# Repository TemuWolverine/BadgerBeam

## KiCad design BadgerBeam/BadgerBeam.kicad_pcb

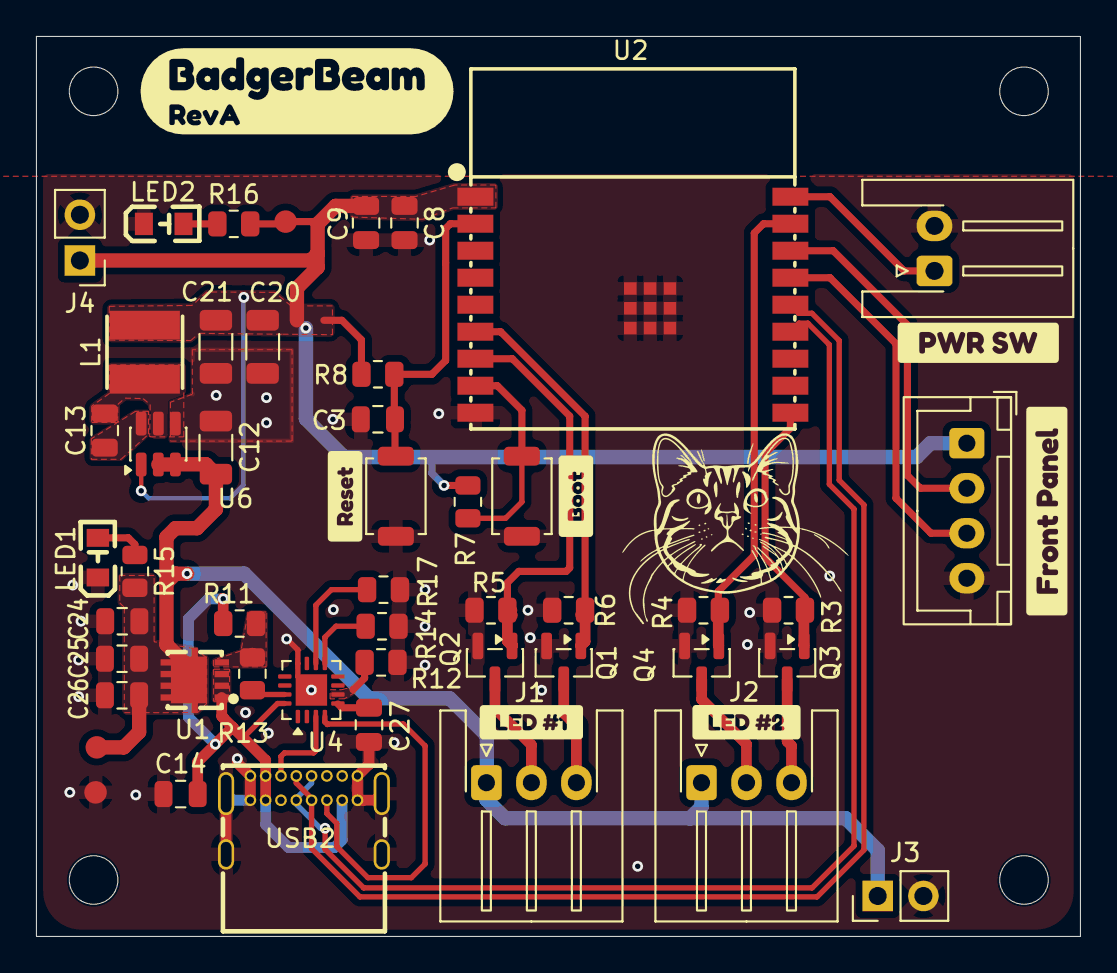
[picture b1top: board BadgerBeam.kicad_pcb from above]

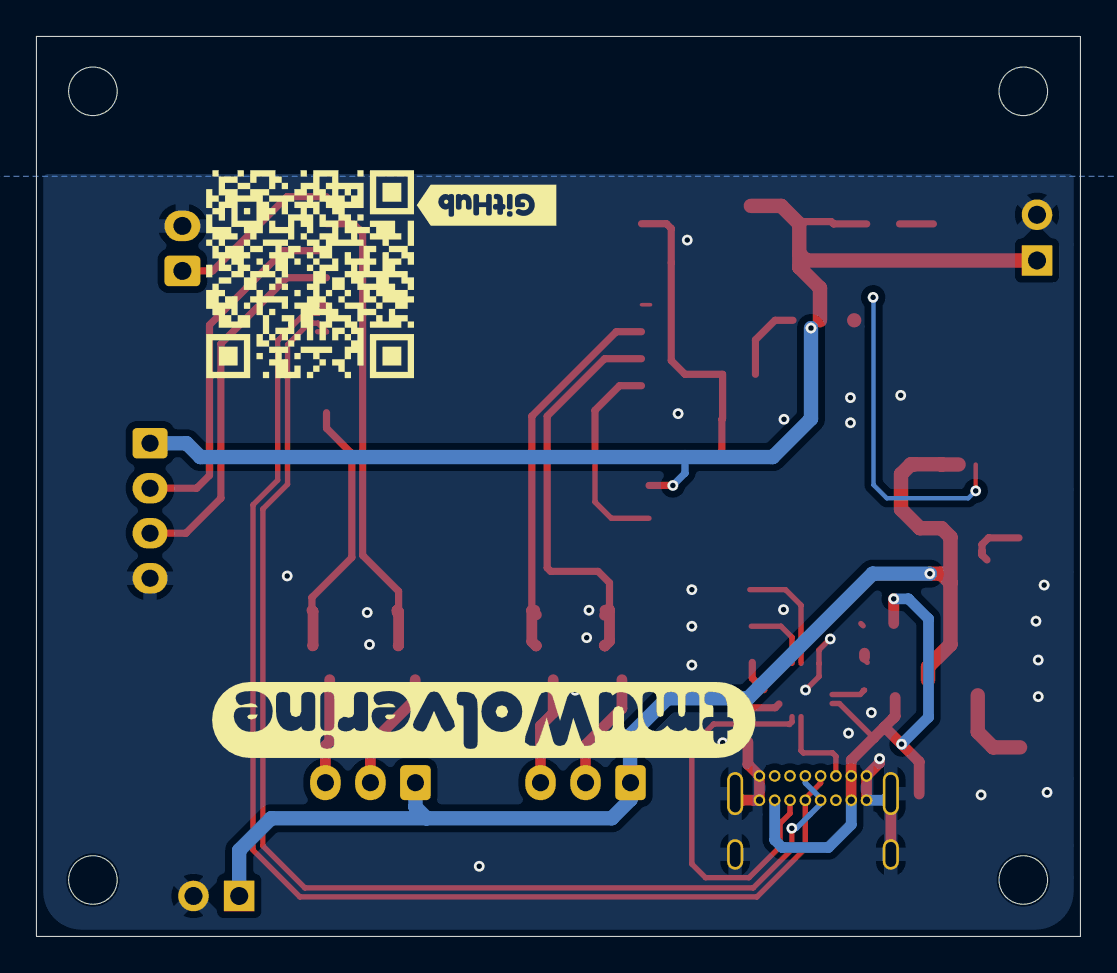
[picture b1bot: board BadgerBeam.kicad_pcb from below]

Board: 2 copper layers, 58.0 x 50.0 mm, 58 parts (3 on the bottom side), 31 nets.

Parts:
C3, C14, C27: 1uF; C_0805_2012Metric
C8: 10uF; C_0805_2012Metric
C9, C13: 100nF; C_0805_2012Metric
C12: 10uF; C_1206_3216Metric
C20, C21: 22uF; C_1206_3216Metric
C24, C25, C26: 4.7uF; C_0805_2012Metric
J1, J2: Conn_01x03_Pin; JST_XH_S3B-XH-A-1_1x03_P2.50mm_Horizontal
J3, J4: Conn_01x02_Pin; PinHeader_1x02_P2.54mm_Vertical
J5: Conn_01x04_Pin; JST_XH_B4B-XH-A_1x04_P2.50mm_Vertical
L1: 3.9μH; IND-SMD_L4.0-W4.0_FNR40XXS
LED1, LED2: LED0805-RD
Q1, Q2, Q3, Q4: AO3400A; SOT-23
R3, R4, R5, R6, R7, R8: 10k; R_0805_2012Metric
R11: 49.9k; R_0805_2012Metric
R12: 900k; R_0805_2012Metric
R13: 5.1k; R_0805_2012Metric
R14, R17: 6.04k; R_0805_2012Metric
R15: 20k; R_0805_2012Metric
R16: 2.4k; R_0805_2012Metric
SW1: SW_Push; JST_XH_S2B-XH-A-1_1x02_P2.50mm_Horizontal
SW3: Reset; SW_SPST_TS-1088-xR020
SW4: Boot; SW_SPST_TS-1088-xR020
TP1, TP2, TP3: TestPoint; TestPoint-1.25mm
U1: PRPAK-8_L3.0-W3.0-P0.65-BL-EP
U2: 2.4GHz; BULETM-SMD_ESPRESSIF_ESP32-C3-WROOM-02-N4-4MB
U4: HUSB238A-xxxxx-QN16R; WQFN-16-1EP_3x3mm_P0.5mm_EP1.75x1.75mm
U6: AP63203WU; TSOT-23-6
USB2: USB-C-TH_UC23-0B16F00P11
kobee-studio-6A97AC47: Kobee Studio; kobee-studio-6A97AC2D
kobee-studio-6A97AC75: Kobee Studio; kobee-studio-6A97AC75
kobee-studio-6AED3B48: Kobee Studio; kobee-studio-6A96C1A4
kobee-studio-6AED3B77: Kobee Studio; kobee-studio-6A97ABF4
kobee-studio-6AF1A8A9, kobee-studio-6AF1A89F, kobee-studio-6AF1A91A, kobee-studio-6AF1A872, kobee-studio-6AF1A910, kobee-studio-6AF03576: Kobee Studio; kobee-studio-6AEAEE22

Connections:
+3V3: C8.1, C9.1, C20.1, C21.1, J4.1, J5.1, L1.2, R7.1, R8.1, R16.2, TP3.1 (1_1), U2.1 (3V3), U6.1 (FB)
/Power/VBUS: C14.2, R11.2, U1.1 (S), U1.2 (S), U1.3 (S), U4.16 (VBUS), USB2.A4 (VBUS), USB2.B4 (VBUS), USB2.B9 (VBUS)
CC1: U4.3 (CC1), USB2.A5 (CC1)
CC2: U4.4 (CC2), USB2.B5 (CC2)
CW_1: Q1.1 (G), R6.2, U2.6 (IO7)
CW_2: Q3.1 (G), R3.1, U2.10 (IO10)
GND: C3.2, C8.2, C9.2, C12.2, C14.1, C20.2, C21.2, C24.2, C25.2, C26.2, C27.1, J3.2, J4.2, J5.4, LED1.1 (K), LED2.1 (K), Q1.2 (S), Q2.2 (S), Q3.2 (S), Q4.2 (S), R3.2, R4.2, R5.2, R6.1, R12.1, R14.2, R17.2, SW1.2, SW3.1, SW4.1, TP1.1 (1_1), U2.9 (GND), U2.19 (EP), U4.12 (~EN), U4.17 (GND), U6.4 (GND), USB2.17 (SHELL), USB2.18 (SHELL), USB2.19 (SHELL), USB2.20 (SHELL), USB2.A1 (GND), USB2.A12 (GND), USB2.B1 (GND), USB2.B12 (GND)
ISET: R17.1, U4.10 (SCL/SNK_ISET)
unnamed: J1.2, Q2.3 (D)
unnamed: J1.3, Q1.3 (D)
unnamed: J2.2, Q4.3 (D)
unnamed: J2.3, Q3.3 (D)
unnamed: J5.2, U2.16 (IO2)
unnamed: J5.3, U2.15 (IO3)
unnamed: LED1.2 (A), R15.1
unnamed: LED2.2 (A), R16.1
unnamed: R11.1, R13.2, U1.4 (G)
unnamed: C3.1, R8.2, SW3.2, U2.2 (EN)
unnamed: SW1.1, U2.18 (IO0)
unnamed: R7.2, SW4.2, U2.8 (IO9)
unnamed: R13.1, U4.15 (GATE)
unnamed: C27.2, U4.5 (VDD)
unnamed: R12.2, U4.6 (~DEBUG)
unnamed: C13.2, U6.6 (BST)
unnamed: C13.1, L1.1, U6.5 (SW)
USBC_D+: U2.14 (IO19), USB2.A6 (DP1), USB2.B6 (DP2)
USBC_D-: U2.13 (IO18), USB2.A7 (DN1), USB2.B7 (DN2)
VDD: C12.1, C24.1, C25.1, C26.1, J1.1, J2.1, J3.1, R15.2, TP2.1 (1_1), U1.5 (D), U1.6 (D), U1.7 (D), U1.8 (D), U6.2 (EN), U6.3 (IN)
VSET: R14.1, U4.9 (SDA/SNK_VSET)
WW_1: Q2.1 (G), R5.1, U2.7 (IO8)
WW_2: Q4.1 (G), R4.1, U2.17 (IO1)

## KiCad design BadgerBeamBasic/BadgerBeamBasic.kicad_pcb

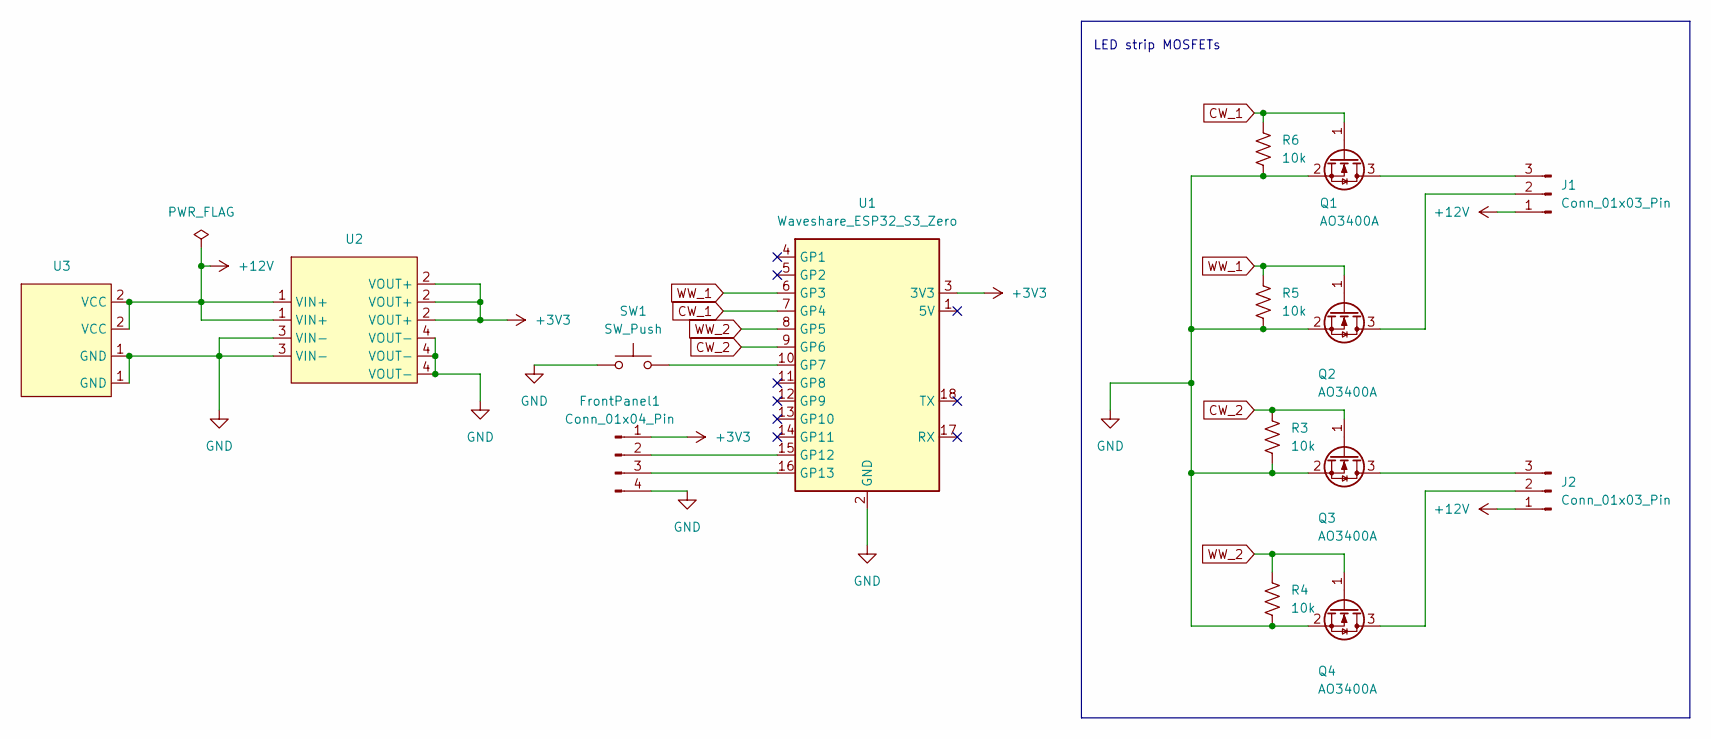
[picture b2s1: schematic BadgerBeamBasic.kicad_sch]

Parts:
FrontPanel1: Conn_01x04_Pin; JST_XH_B4B-XH-A_1x04_P2.50mm_Vertical
J1, J2: Conn_01x03_Pin; JST_XH_S3B-XH-A-1_1x03_P2.50mm_Horizontal
Q1, Q2, Q3, Q4: AO3400A; SOT-23
R3, R4, R5, R6: 10k; R_Axial_DIN0204_L3.6mm_D1.6mm_P2.54mm_Vertical
SW1: SW_Push; JST_XH_S2B-XH-A-1_1x02_P2.50mm_Horizontal
U1: Waveshare_ESP32_S3_Zero; Waveshare_ESP32_S3_Zero_SMD
U2: WaveshareDCDCBuck
U3: USB-PD-Breakout

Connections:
+3V3: FrontPanel1.1, U1.3 (3V3), U2.2 (VOUT+)
+12V: J1.1, J2.1, U2.1 (VIN+), U3.2 (VCC)
CW_1: Q1.1 (G), R6.2, U1.7 (GP4)
CW_2: Q3.1 (G), R3.1, U1.9 (GP6)
GND: FrontPanel1.4, Q1.2 (S), Q2.2 (S), Q3.2 (S), Q4.2 (S), R3.2, R4.2, R5.2, R6.1, SW1.1, U1.2 (GND), U2.3 (VIN-), U2.4 (VOUT-), U3.1 (GND)
unnamed: FrontPanel1.2, U1.15 (GP12)
unnamed: FrontPanel1.3, U1.16 (GP13)
unnamed: J1.2, Q2.3 (D)
unnamed: J1.3, Q1.3 (D)
unnamed: J2.2, Q4.3 (D)
unnamed: J2.3, Q3.3 (D)
unnamed: SW1.2, U1.10 (GP7)
WW_1: Q2.1 (G), R5.1, U1.6 (GP3)
WW_2: Q4.1 (G), R4.1, U1.8 (GP5)

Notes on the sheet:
LED strip MOSFETs

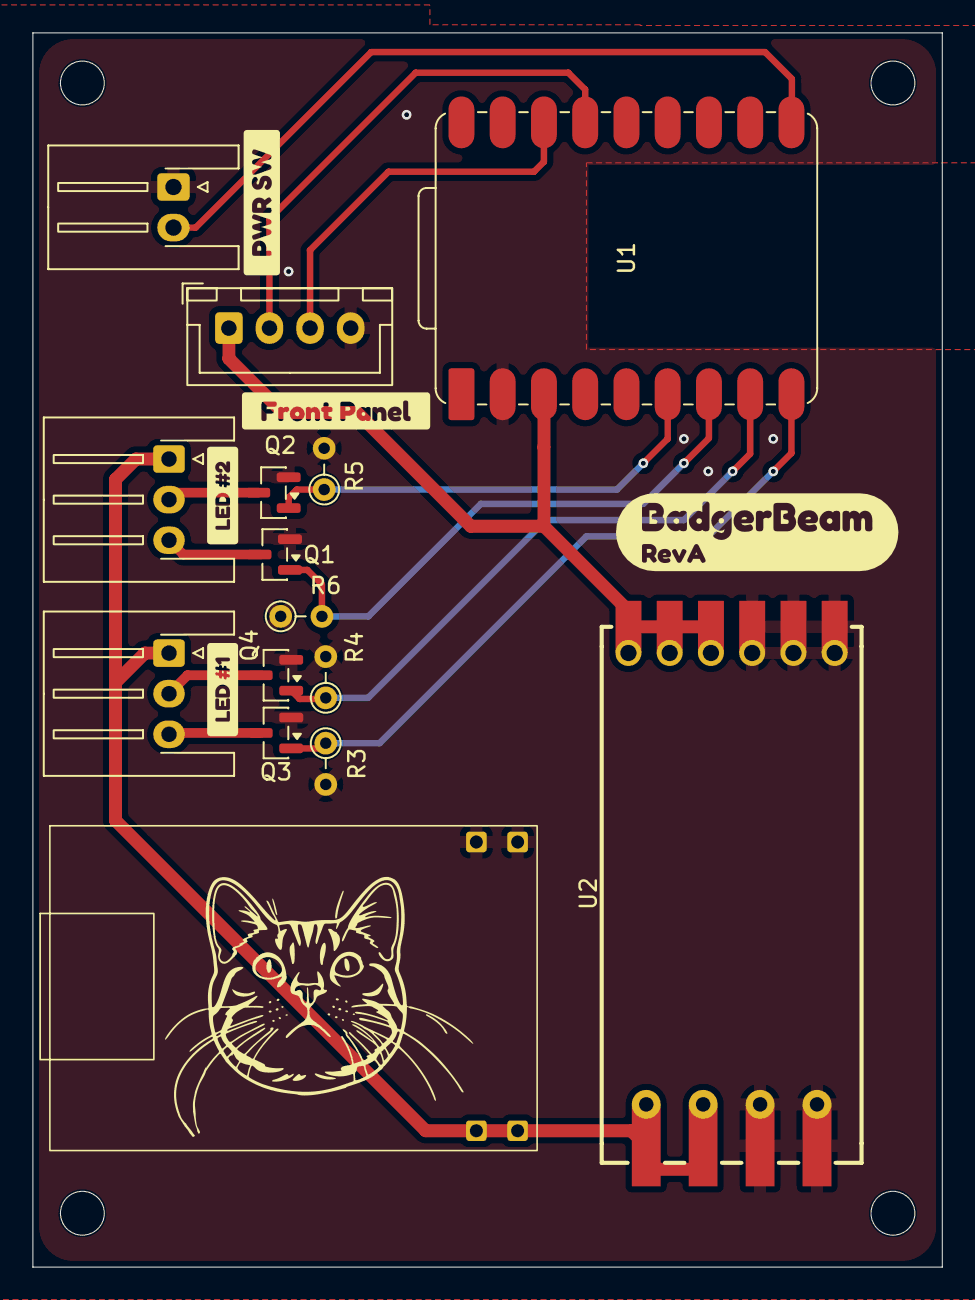
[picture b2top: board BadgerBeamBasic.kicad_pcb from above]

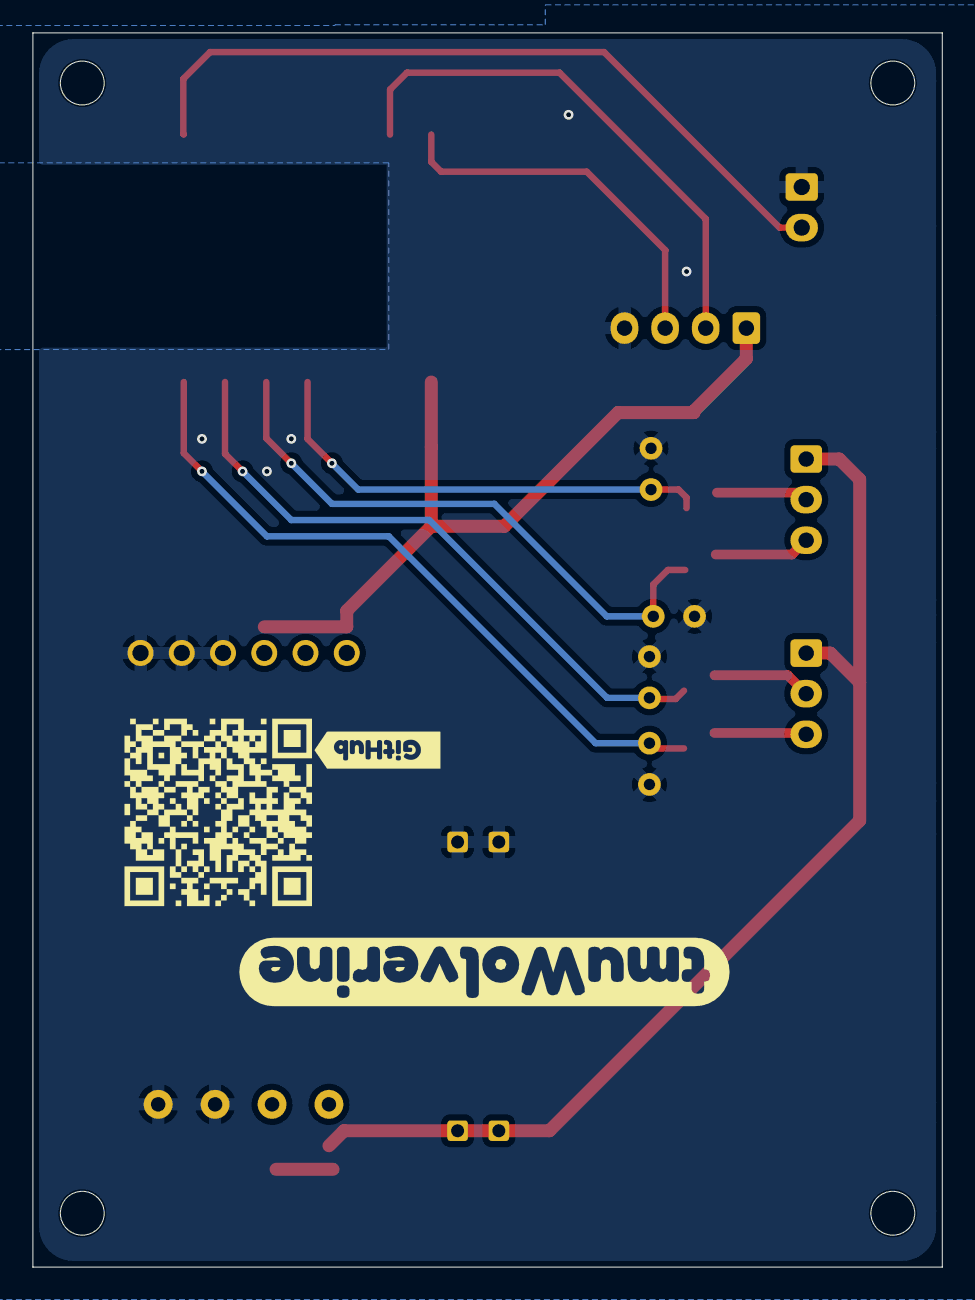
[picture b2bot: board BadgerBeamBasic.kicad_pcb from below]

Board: 2 copper layers, 56.0 x 76.0 mm, 23 parts (3 on the bottom side), 14 nets.

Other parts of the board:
kobee-studio-6A97AC47: Kobee Studio; kobee-studio-6A97AC2D
kobee-studio-6A97AC75: Kobee Studio; kobee-studio-6A97AC75
kobee-studio-6AED3B48: Kobee Studio; kobee-studio-6A96C1A4
kobee-studio-6AF1A8A9, kobee-studio-6AF1A89F, kobee-studio-6AF1A872, kobee-studio-6AF03576: Kobee Studio; kobee-studio-6AEAEE22
kobee-studio-6AF02C0C: Kobee Studio; kobee-studio-6A97ABF4

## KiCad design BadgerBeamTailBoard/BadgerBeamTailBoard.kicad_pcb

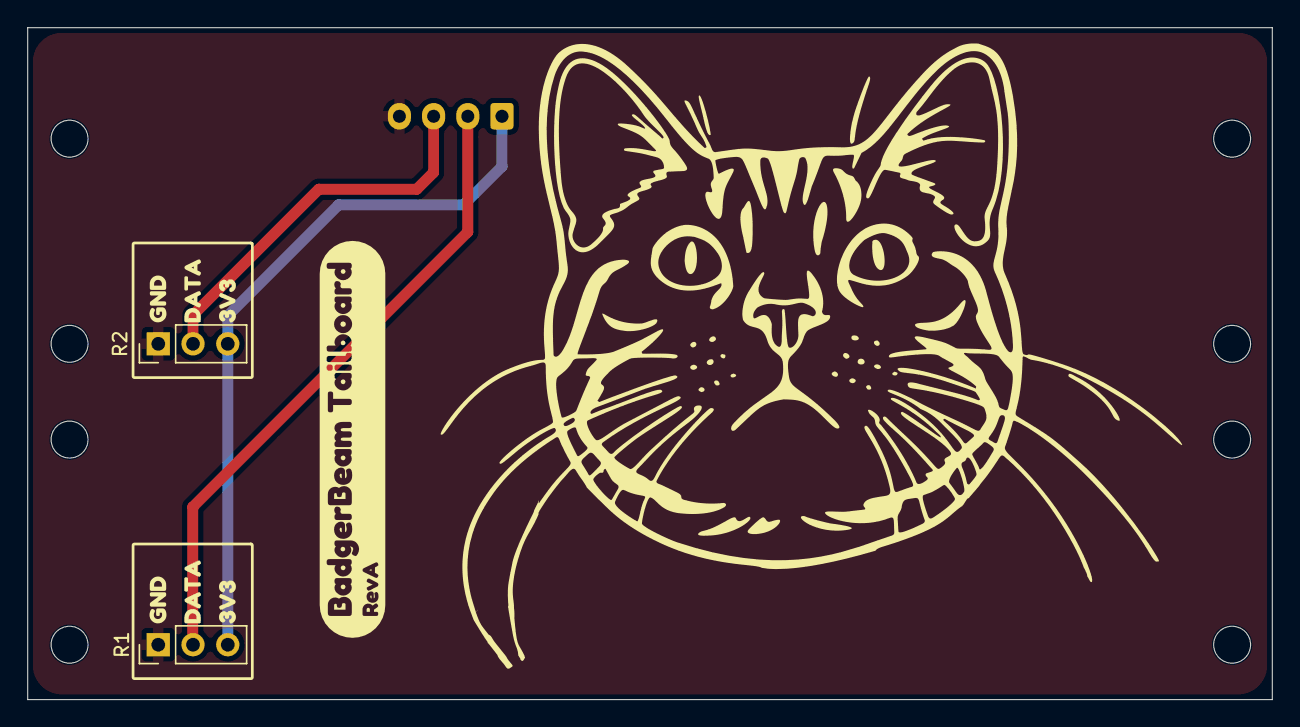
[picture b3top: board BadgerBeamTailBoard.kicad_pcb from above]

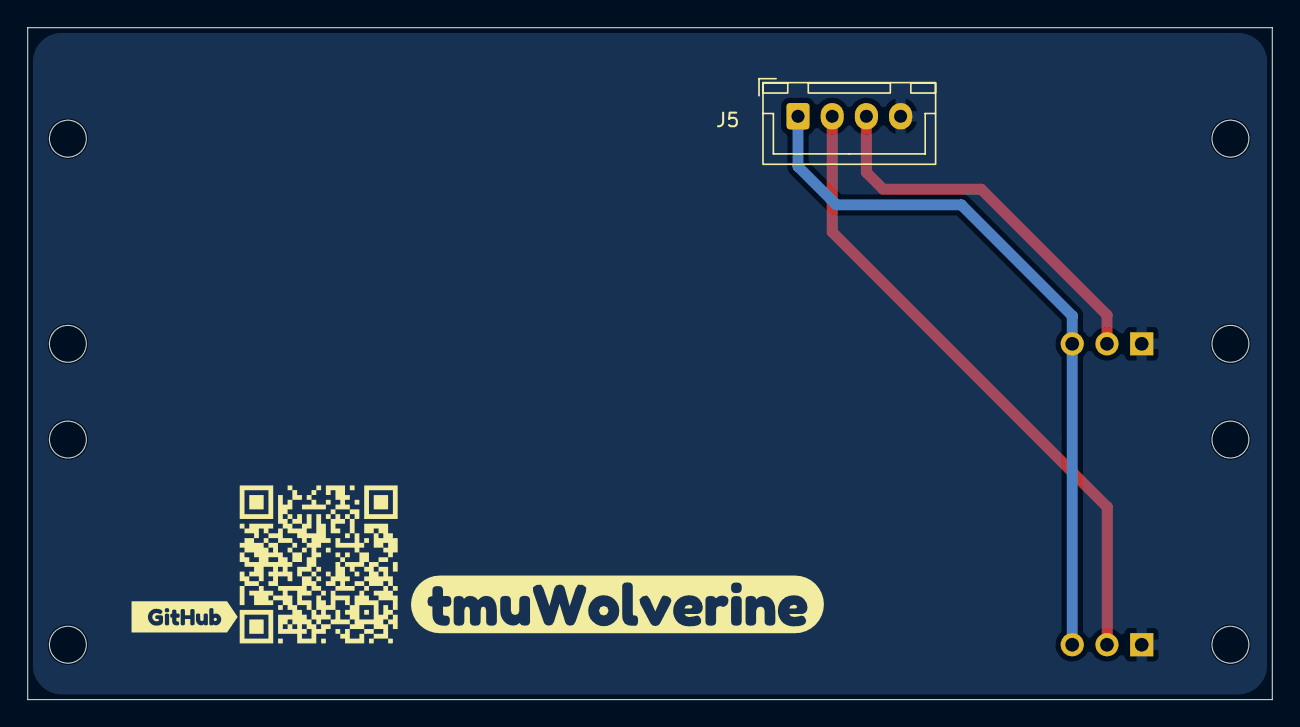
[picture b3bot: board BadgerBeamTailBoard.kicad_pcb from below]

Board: 2 copper layers, 91.0 x 49.1 mm, 9 parts (4 on the bottom side), 4 nets.

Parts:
J5: Conn_01x04_Pin; JST_XH_B4B-XH-A_1x04_P2.50mm_Vertical
R1, R2: 10k Linear; PinHeader_1x03_P2.54mm_Vertical
kobee-studio-6A97AC47: Kobee Studio; kobee-studio-6A97AC2D
kobee-studio-6A97AC75: Kobee Studio; kobee-studio-6A97AC75
kobee-studio-6AED3B77: Kobee Studio; kobee-studio-6A97ABF4
kobee-studio-6AEEF65B, kobee-studio-6AEEF663: Kobee Studio; kobee-studio-6AEEF55F
kobee-studio-6AEEF464: Kobee Studio; kobee-studio-6A96C1A4

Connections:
+3V3: J5.1, R1.3, R2.3
GND: J5.4, R1.1, R2.1
unnamed: J5.2, R1.2 (2_2)
unnamed: J5.3, R2.2 (2_2)
